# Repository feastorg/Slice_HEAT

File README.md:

# DC heating Element Controller Slice

DC heating Element Controller Slice for BREAD.

## Introduction

[Short introduction on the project.]

## Usage

[Explain how to use the project. Include examples and screenshots if applicable.]

## Documentation

Please refer to the [docs](/docs) for more info.

---

<div align="center">
  
</div>

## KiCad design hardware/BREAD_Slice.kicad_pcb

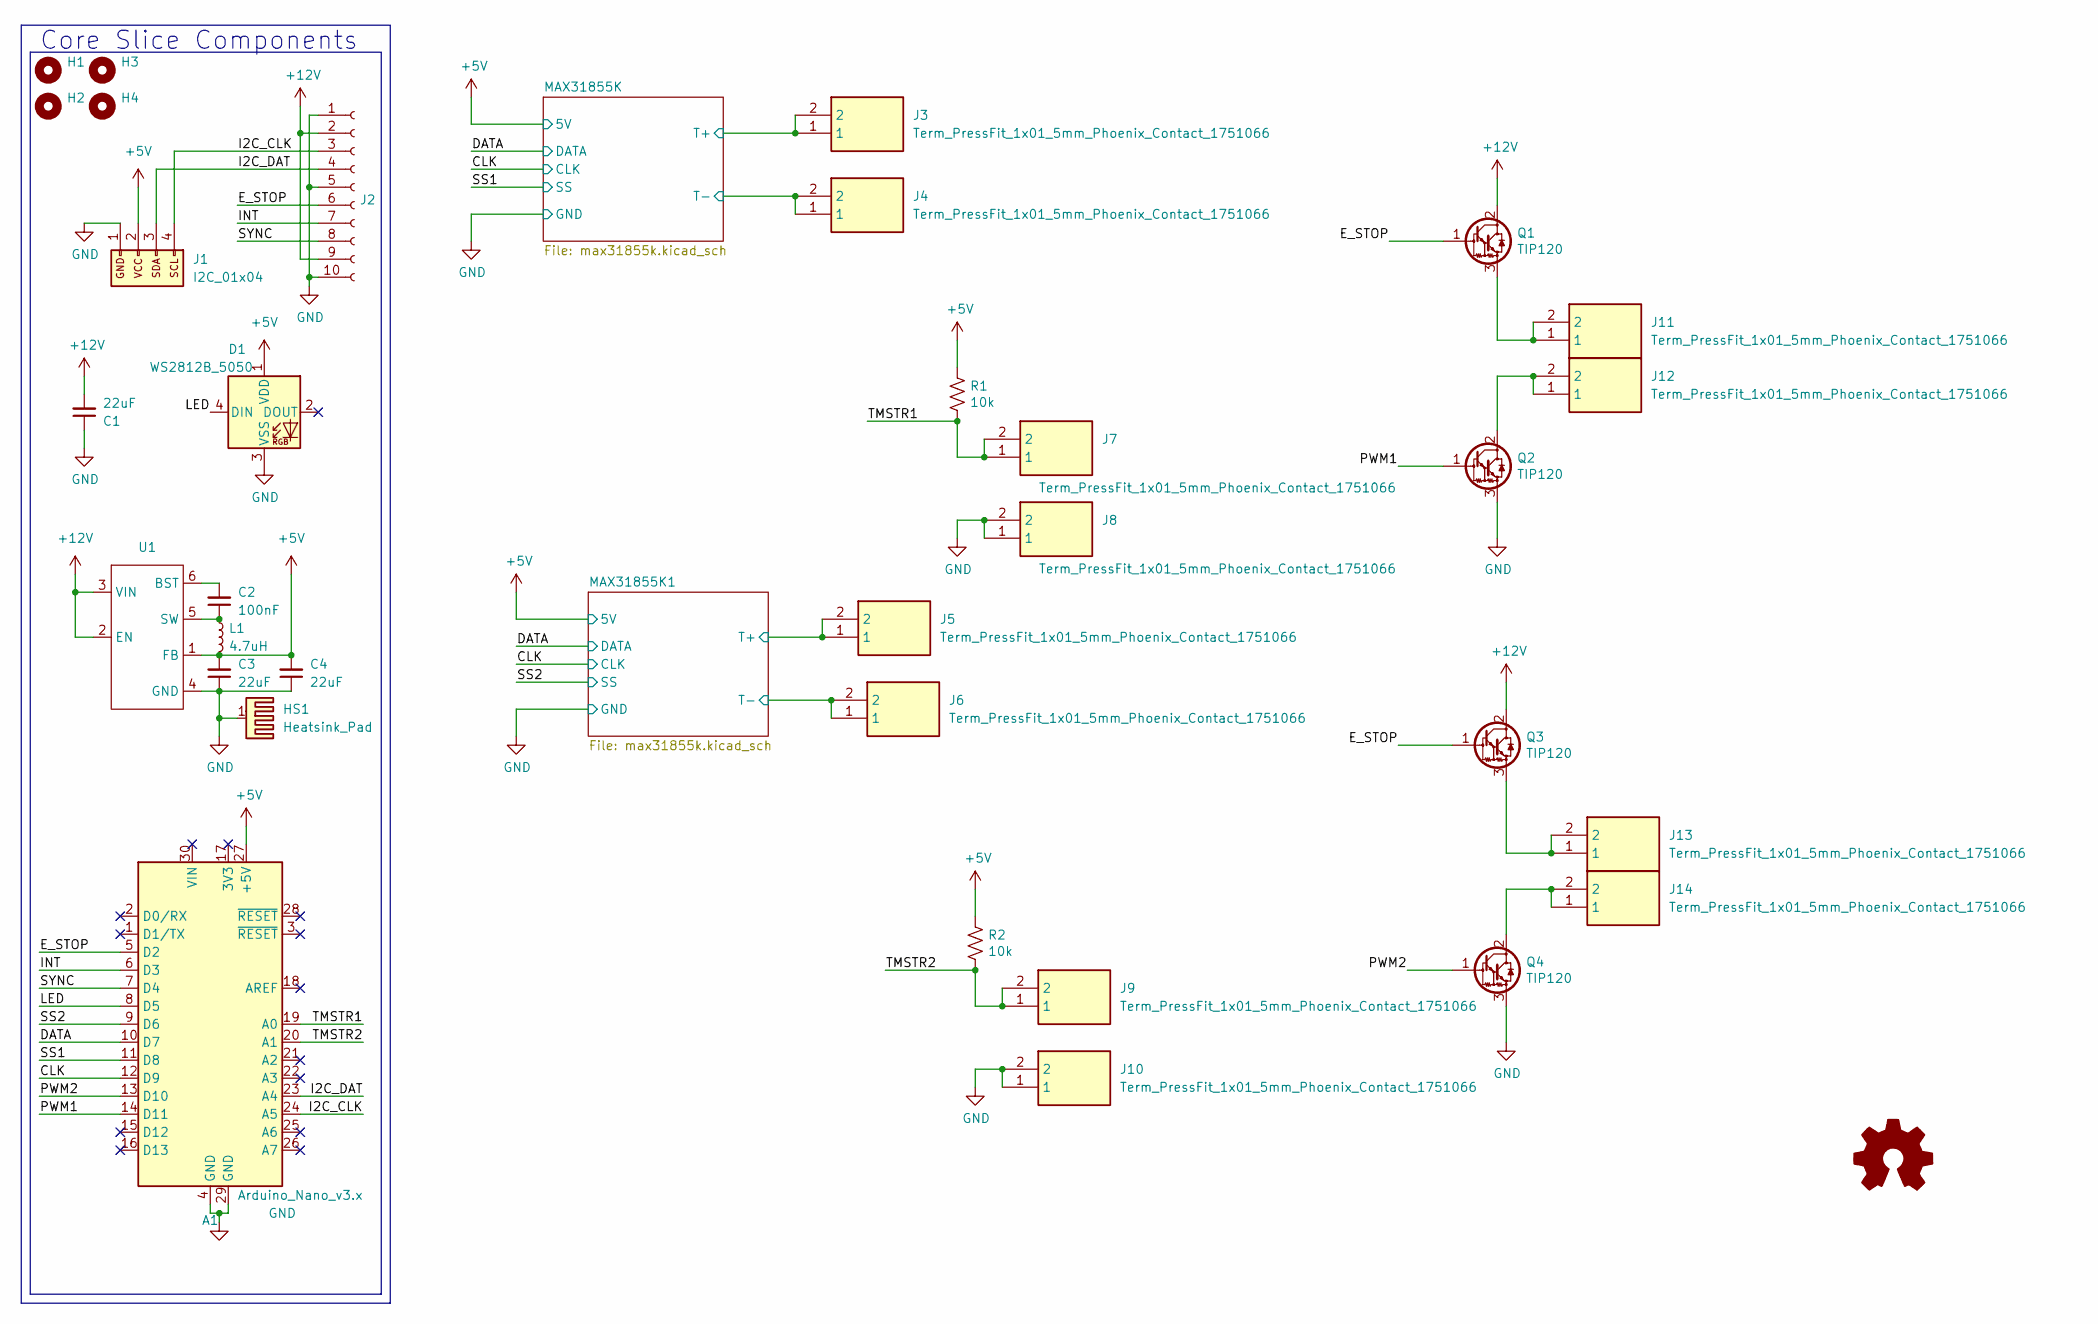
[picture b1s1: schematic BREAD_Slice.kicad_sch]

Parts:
A1: Arduino_Nano_v3.x; Arduino_Nano
C1, C3, C4: 22uF; C_1206_3216Metric
C2: 100nF; C_1206_3216Metric
D1: WS2812B_5050; WS2812-5050-4PIN
H1, H2, H3, H4: MountingHole; MountingHole_5mm
HS1: Heatsink_Pad; Thermal_Pad
J1: I2C_01x04; JST_SH_SM04B-SRSS-TB_1x04-1MP_P1.00mm_Horizontal
J2: Conn_01x10_Female; PinSocket_1x10_P2.54mm_Horizontal
J3, J4, J5, J6, J7, J8, J9, J10, J11, J12, J13, J14: Term_PressFit_1x01_5mm_Phoenix_Contact_1751066; 1751066; Manufacturer_Part_Number 1751066
L1: 4.7uH; L_1210_3225Metric
Q1, Q2: TIP120; TO-220-3_Horizontal_TabDown
Q3, Q4: TIP120; TO-220-3_Horizontal_TabUp
R1, R2: 10k; R_1206_3216Metric_Pad1.30x1.75mm_HandSolder
U1: TSOT-23-6

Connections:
+5V: A1.27 (+5V), C3.2, C4.2, D1.1 (VDD), J1.2, L1.2, R1.1, R2.1, U1.1 (FB); also elsewhere on the board
+12V: C1.2, J2.2, J2.9, Q1.2 (C), Q3.2 (C), U1.2 (EN), U1.3 (VIN)
/CLK: A1.12 (D9); also elsewhere on the board
/DATA: A1.10 (D7); also elsewhere on the board
/E_STOP: A1.5 (D2), J2.6, Q1.1 (B), Q3.1 (B)
/I2C_CLK: A1.24 (A5), J1.4, J2.3
/I2C_DAT: A1.23 (A4), J1.3, J2.4
/INT: A1.6 (D3), J2.7
/LED: A1.8 (D5), D1.4 (DIN)
/MAX31855K1/T+: J5.1, J5.2; also elsewhere on the board
/MAX31855K1/T-: J6.1, J6.2; also elsewhere on the board
/MAX31855K/T+: J3.1, J3.2; also elsewhere on the board
/MAX31855K/T-: J4.1, J4.2; also elsewhere on the board
/PWM1: A1.14 (D11), Q2.1 (B)
/PWM2: A1.13 (D10), Q4.1 (B)
/SS1: A1.11 (D8); also elsewhere on the board
/SS2: A1.9 (D6); also elsewhere on the board
/SYNC: A1.7 (D4), J2.8
/TMSTR1: A1.19 (A0), J7.1, J7.2, R1.2
/TMSTR2: A1.20 (A1), J9.1, J9.2, R2.2
GND: A1.4 (GND), A1.29 (GND), C1.1, C3.1, C4.1, D1.3 (VSS), HS1.1, J1.1, J2.1, J2.5, J2.10, J8.1, J8.2, J10.1, J10.2, Q2.3 (E), Q4.3 (E), U1.4 (GND); also elsewhere on the board
unnamed: J11.1, J11.2, Q1.3 (E)
unnamed: J12.1, J12.2, Q2.2 (C)
unnamed: J13.1, J13.2, Q3.3 (E)
unnamed: J14.1, J14.2, Q4.2 (C)
unnamed: C2.2, U1.6 (BST)
unnamed: C2.1, L1.1, U1.5 (SW)

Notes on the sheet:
Core Slice Components

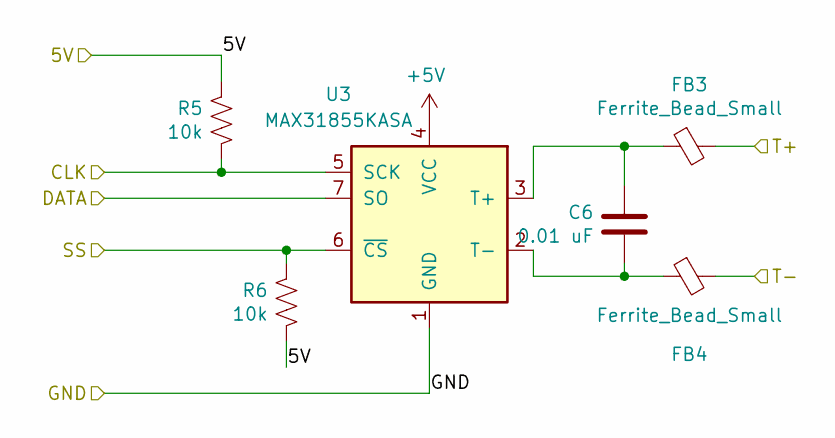
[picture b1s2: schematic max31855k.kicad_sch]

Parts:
C6: 0.01 uF; C_1206_3216Metric_Pad1.33x1.80mm_HandSolder
FB3, FB4: Ferrite_Bead_Small; R_1206_3216Metric_Pad1.30x1.75mm_HandSolder
R5, R6: 10k; R_1206_3216Metric_Pad1.30x1.75mm_HandSolder
U3: MAX31855KASA; SOIC-8_3.9x4.9mm_P1.27mm

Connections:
+5V: R5.1, R6.2, U3.4 (VCC); also elsewhere on the board
/CLK: R5.2, U3.5 (SCK); also elsewhere on the board
/DATA: U3.7 (SO); also elsewhere on the board
/MAX31855K1/T+: FB3.2; also elsewhere on the board
/MAX31855K1/T-: FB4.2; also elsewhere on the board
/SS2: R6.1, U3.6 (~CS); also elsewhere on the board
GND: U3.1 (GND); also elsewhere on the board
unnamed: C6.1, FB3.1, U3.3 (T+)
unnamed: C6.2, FB4.1, U3.2 (T-)

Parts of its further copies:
C5: 0.01 uF; C_1206_3216Metric_Pad1.33x1.80mm_HandSolder
FB1, FB2: Ferrite_Bead_Small; R_1206_3216Metric_Pad1.30x1.75mm_HandSolder
R3, R4: 10k; R_1206_3216Metric_Pad1.30x1.75mm_HandSolder
U2: MAX31855KASA; SOIC-8_3.9x4.9mm_P1.27mm

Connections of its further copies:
+5V: R3.1, R4.2, U2.4 (VCC); also elsewhere on the board
/CLK: R3.2, U2.5 (SCK); also elsewhere on the board
/DATA: U2.7 (SO); also elsewhere on the board
/MAX31855K/T+: FB1.2; also elsewhere on the board
/MAX31855K/T-: FB2.2; also elsewhere on the board
/SS1: R4.1, U2.6 (~CS); also elsewhere on the board
GND: U2.1 (GND); also elsewhere on the board
unnamed: C5.1, FB1.1, U2.3 (T+)
unnamed: C5.2, FB2.1, U2.2 (T-)

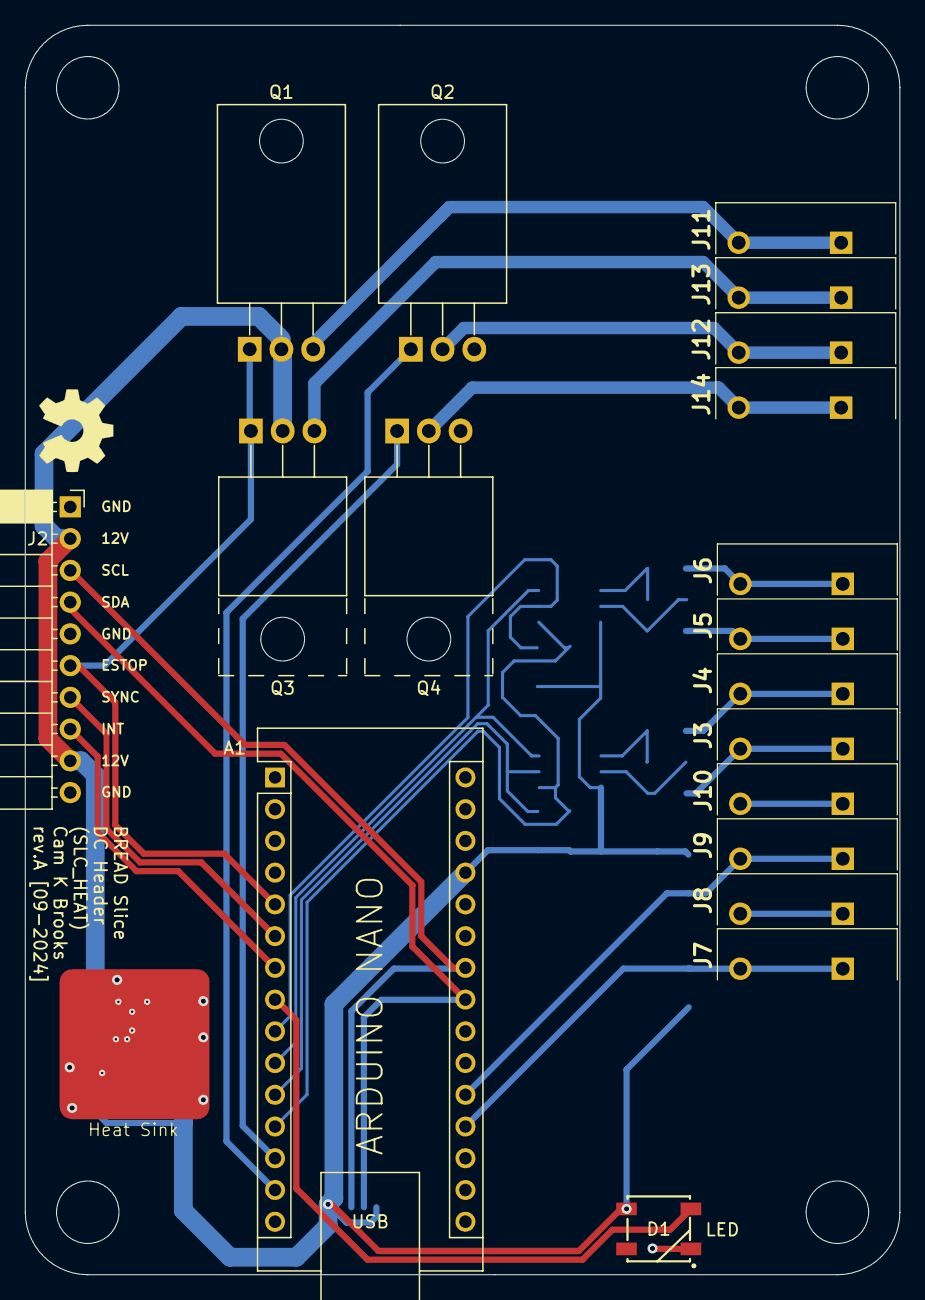
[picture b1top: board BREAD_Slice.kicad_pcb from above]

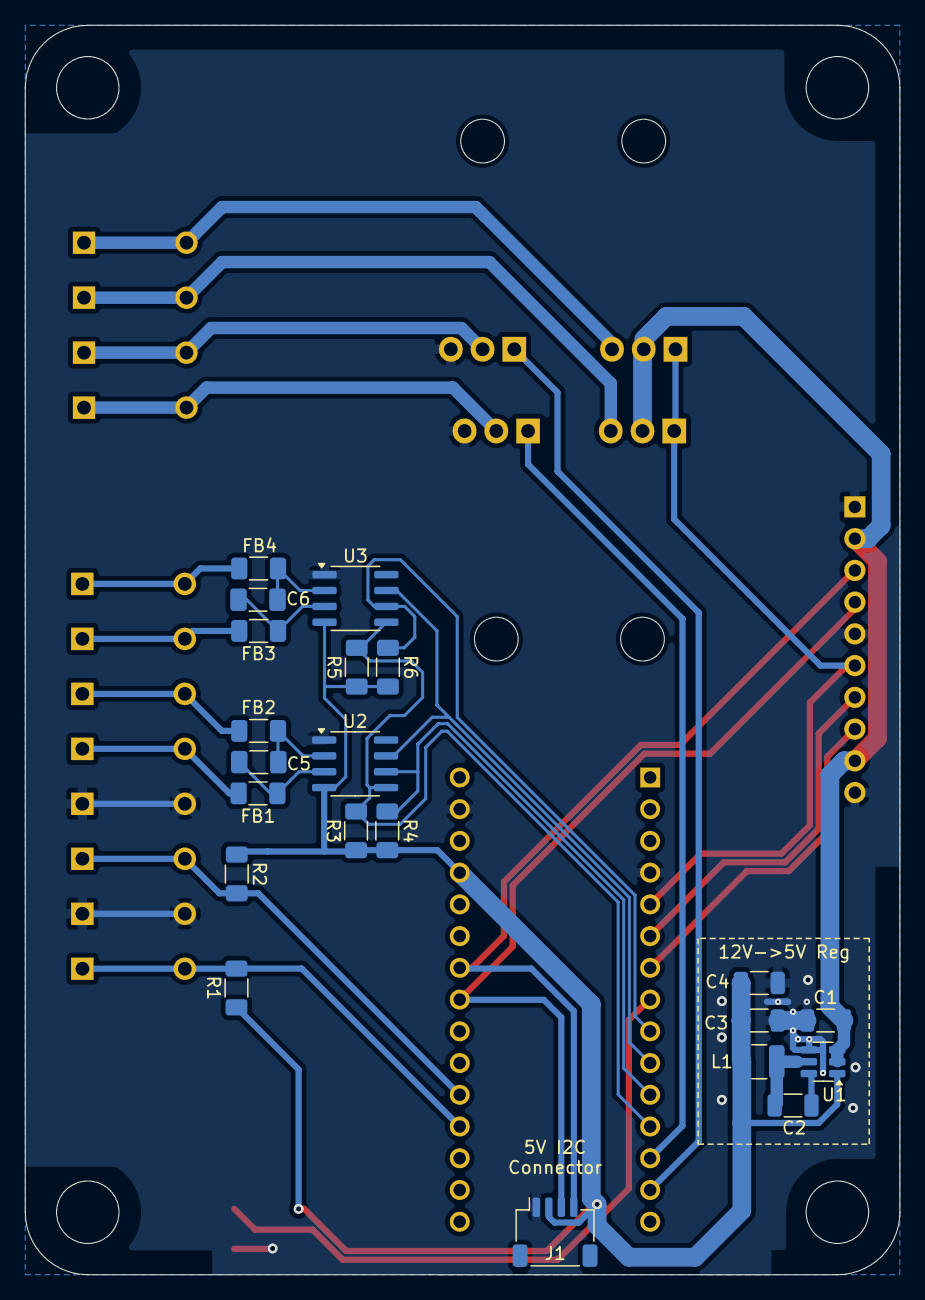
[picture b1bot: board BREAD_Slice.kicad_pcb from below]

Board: 2 copper layers, 70.0 x 100.0 mm, 46 parts (21 on the bottom side), 31 nets.

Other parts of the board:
Logo1: Logo_Open_Hardware_Small; OSHW-Symbol_6.7x6mm_SilkScreen

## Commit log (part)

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2024-09-10 set repo
2024-09-10 upgraded by duplicating ciruit, new core, all back copper
2024-09-10 firmware files fix
2024-09-10 removed old design
2024-09-12 minor fixes
2024-09-12 updated to the correct terminals and proper hierarchial pages
2024-09-30 JLCPCB order rev-A
2026-04-18 chore: minor updates
2026-04-18 chore: update to kicad9
2026-04-18 chore: add error sev.
2026-05-20 Add slice.yaml manifest (schema v1.0)
2026-05-24 Add KiBot/docs pipeline
2026-05-24 Update TODO with CI findings (ERC errors)
